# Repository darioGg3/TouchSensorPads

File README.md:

# 4_Touch_Sensor_Board
PCB con 4 pads capacitivos configurable y comunicacion a traves e GPIOs.

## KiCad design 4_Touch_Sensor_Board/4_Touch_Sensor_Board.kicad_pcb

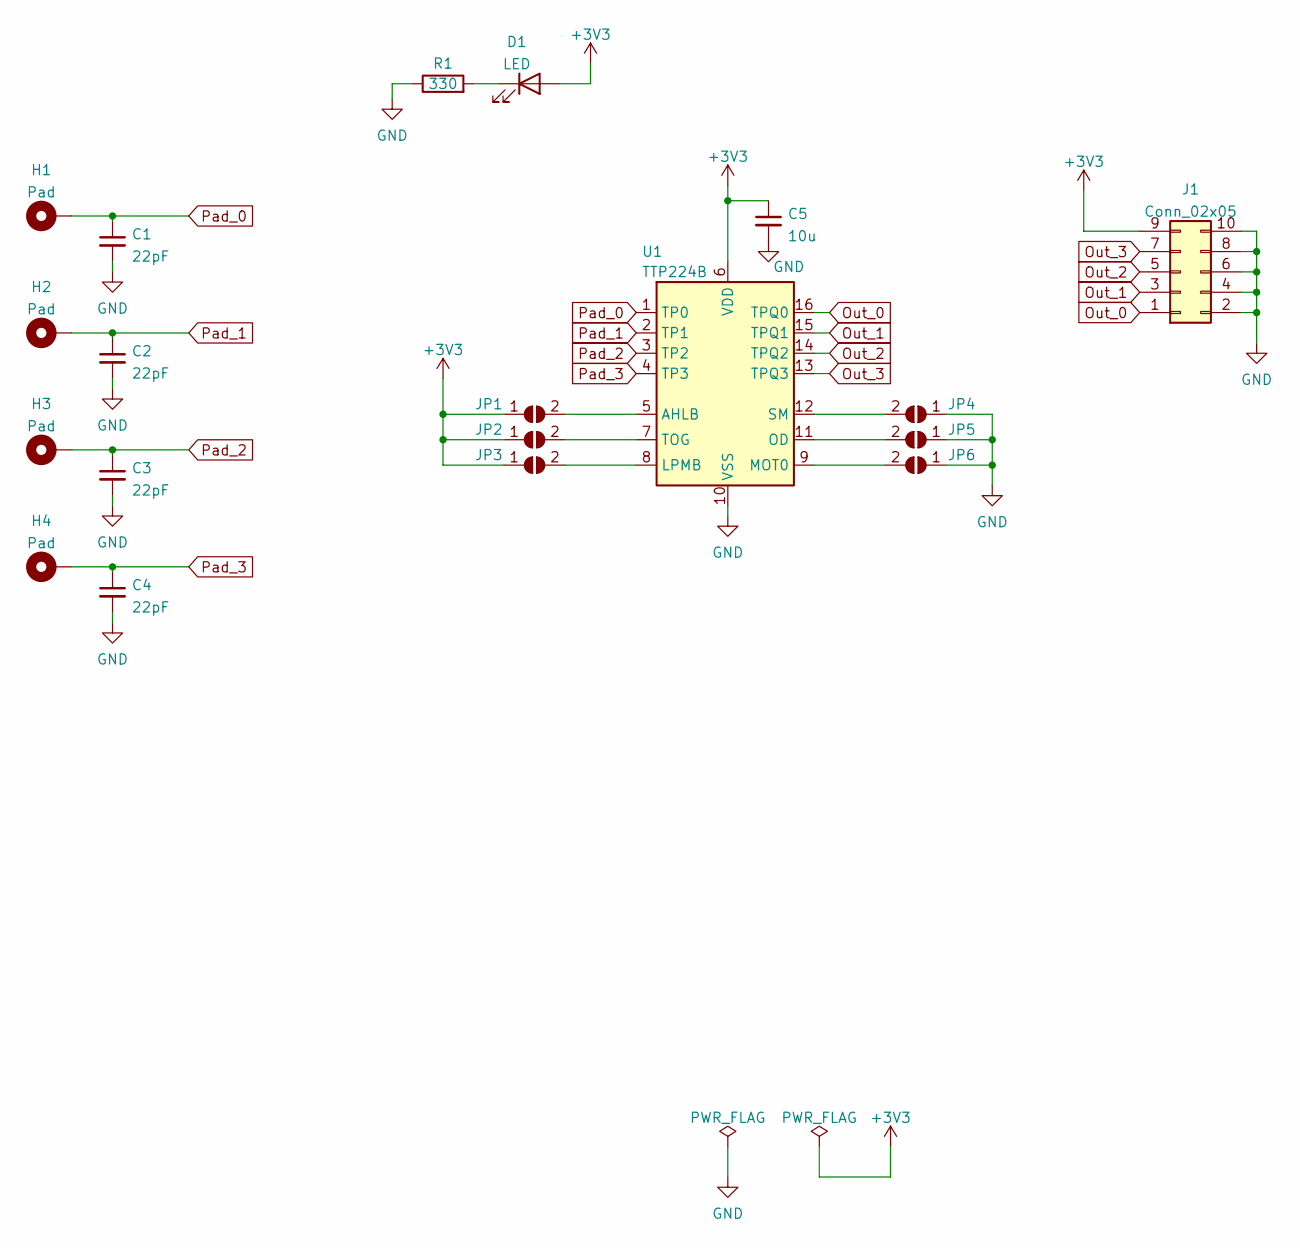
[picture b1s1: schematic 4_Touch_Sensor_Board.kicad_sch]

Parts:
C1, C2, C3, C4: 22pF; C_0603_1608Metric
C5: 10u; C_0603_1608Metric
D1: LED; LED_0603_1608Metric
H1, H3: Pad; FingerPrint_Pad_SolderMask
H2, H4: Pad; FingerPrint_Pad_Silk
J1: Conn_02x05; IDC-Header_2x05_P2.54mm_Vertical
JP1, JP2, JP3, JP4, JP5, JP6: SolderJumper-2_P1.3mm_Open_TrianglePad1.0x1.5mm
R1: 330; R_0402_1005Metric
U1: TTP224B

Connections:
+3V3: C5.1, D1.2 (A), J1.9, JP1.1 (A), JP2.1 (A), JP3.1 (A), U1.6 (VDD)
GND: C1.2, C2.2, C3.2, C4.2, C5.2, J1.2, J1.4, J1.6, J1.8, J1.10, JP4.1 (A), JP5.1 (A), JP6.1 (A), R1.1, U1.10 (VSS)
unnamed: D1.1 (K), R1.2
unnamed: JP1.2 (B), U1.5 (AHLB)
unnamed: JP2.2 (B), U1.7 (TOG)
unnamed: JP3.2 (B), U1.8 (LPMB)
unnamed: JP4.2 (B), U1.12 (SM)
unnamed: JP5.2 (B), U1.11 (OD)
unnamed: JP6.2 (B), U1.9 (MOT0)
Out_0: J1.1, U1.16 (TPQ0)
Out_1: J1.3, U1.15 (TPQ1)
Out_2: J1.5, U1.14 (TPQ2)
Out_3: J1.7, U1.13 (TPQ3)
Pad_0: C1.1, H1.1, U1.1 (TP0)
Pad_1: C2.1, H2.1, U1.2 (TP1)
Pad_2: C3.1, H3.1, U1.3 (TP2)
Pad_3: C4.1, H4.1, U1.4 (TP3)

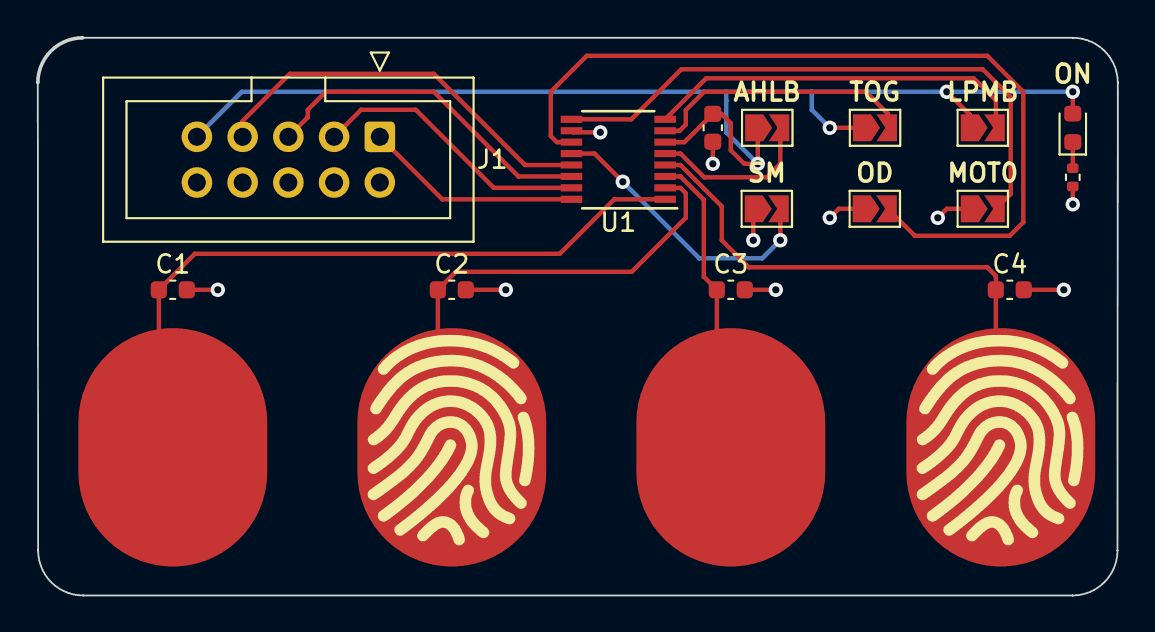
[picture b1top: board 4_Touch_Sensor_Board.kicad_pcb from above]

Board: 2 copper layers, 60.0 x 30.9 mm, 19 parts (0 on the bottom side), 17 nets.

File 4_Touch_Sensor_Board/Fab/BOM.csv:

"Id";"Identificador";"Paquete";"Cantidad";"Identificación";"Suministrador y ref";
1;"C2,C4,C1,C3";"C_0603_1608Metric";4;"22pF";;;
2;"JP6,JP1,JP2,JP5,JP3,JP4";"SolderJumper-2_P1.3mm_Open_TrianglePad1.0x1.5mm";6;" ";;;
3;"R1";"R_0402_1005Metric";1;"330";;;
4;"U1";"SSOP-16_3.9x4.9mm_P0.635mm";1;"TTP224B";;;
5;"H2,H4";"FingerPrint_Pad_Silk";2;"Pad";;;
6;"H1,H3";"FingerPrint_Pad_SolderMask";2;"Pad";;;
7;"C5";"C_0603_1608Metric";1;"10u";;;
8;"D1";"LED_0603_1608Metric";1;"LED";;;
9;"REF**";"OSHW-Logo2_14.6x12mm_SilkScreen";1;"OSHW-Logo2_14.6x12mm_SilkScreen";;;
10;"REF**";"KiCad-Logo2_8mm_SilkScreen";1;"KiCad-Logo2_8mm_SilkScreen";;;

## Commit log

2022-01-26 Design V1.0
2022-02-23 fix board file and add BOM an POS files to JLCPCB
2022-02-23 gerber actualizacion
2022-04-29 changes to upload
2022-09-01 updated fab files
